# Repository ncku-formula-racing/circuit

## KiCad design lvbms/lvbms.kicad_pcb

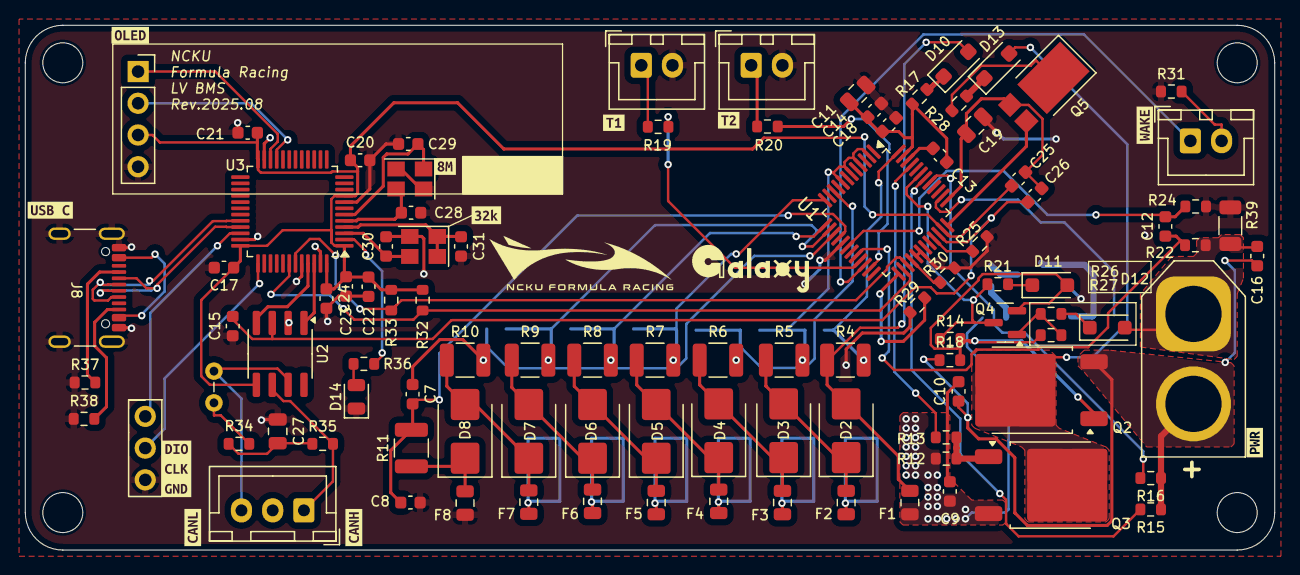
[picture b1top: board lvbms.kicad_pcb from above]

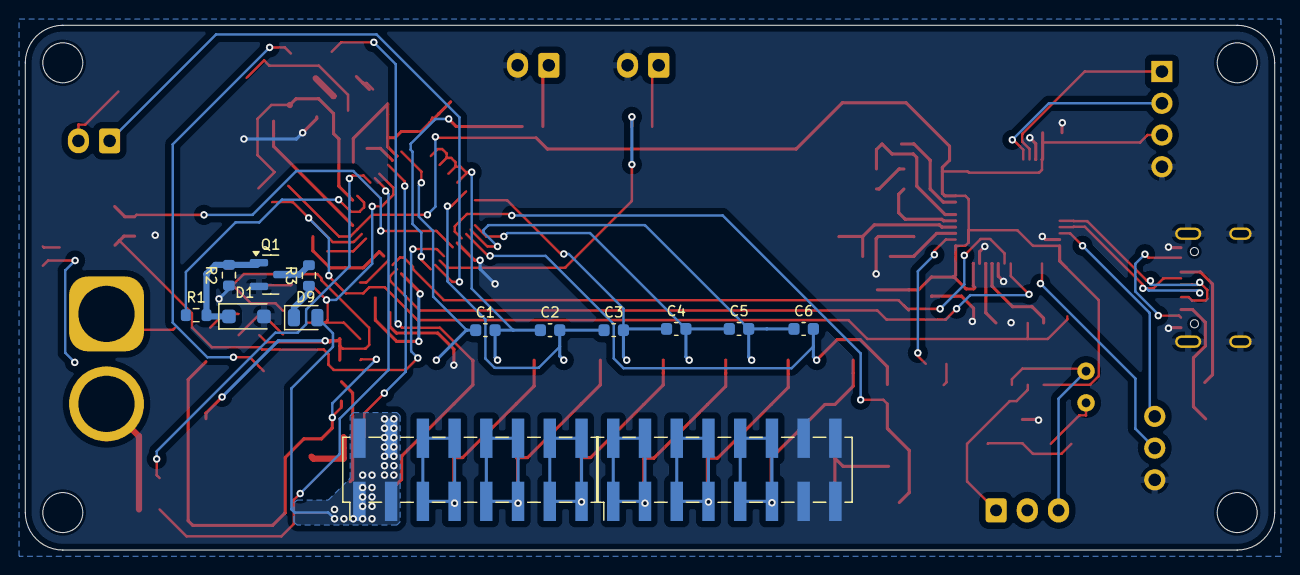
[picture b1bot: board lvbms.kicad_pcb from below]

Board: 2 copper layers, 100.0 x 42.0 mm, 127 parts (14 on the bottom side), 83 nets.

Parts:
C1, C2, C3, C4, C5, C6, C7, C8: 220n; C_0603_1608Metric
C9, C10, C12, C15, C16, C17, C20, C21, C22, C23, C24: 100n; C_0603_1608Metric
C11, C19, C27: 1u; C_0805_2012Metric
C13, C14: 470n; C_0603_1608Metric
C18: 100p; C_0603_1608Metric
C25, C26: 22n; C_0603_1608Metric
C28, C29, C30, C31: 20p; C_0603_1608Metric
D1: BZT52C6V2-13-F; D_SOD-123F
D2, D3, D4, D5, D6, D7, D8: SMBJ55.0CA; D_SMB
D9: PWR_LED; LED_0805_2012Metric
D10, D11, D12, D13: BAT46W-7-F; D_SOD-123F
D14: RUN_GREEN; LED_0805_2012Metric
F1, F2, F3, F4, F5, F6, F7, F8: 0.5A Fuse; Fuse_0805_2012Metric
H1, H2, H3, H4: MountingHole; MountingHole_3.2mm_M3_DIN965
J1: Conn_T1; JST_XH_B2B-XH-A_1x02_P2.50mm_Vertical
J2: Conn_T2; JST_XH_B2B-XH-A_1x02_P2.50mm_Vertical
J3: Conn_PWR; AMASS_XT60-M_1x02_P7.20mm_Vertical
J4: Conn_CAN; JST_XH_B3B-XH-A_1x03_P2.50mm_Vertical
J5: Conn_WAKE; JST_XH_B2B-XH-A_1x02_P2.50mm_Vertical
J6: Conn_OLED; PinSocket_1x04_P2.54mm_Vertical
J7: PROG; PinHeader_1x03_P2.54mm_Vertical
J8: USB_C_Receptacle_USB2.0_16P; USB_C_Receptacle_GCT_USB4105-xx-A_16P_TopMnt_Horizontal
J9, J10: Conn_02x08_Counter_Clockwise; PinHeader_2x08_P2.54mm_Vertical_SMD
JP1: Jumper_2_Open; Jumper_P2.54mm_D0.7mm
Q1, Q4: 2N7002; SOT-23
Q2, Q3: DMN6040SK3; TO-252-2
Q5: DXT5551P5; D_PowerDI-5
R1, R13, R37, R38: 5k1; R_0603_1608Metric
R2: 20k; R_0603_1608Metric
R3, R14, R15, R16, R19, R20, R26, R31, R32, R33: 10k; R_0603_1608Metric
R4, R5, R6, R7, R8, R9, R10, R11: 100R; R_1210_3225Metric
R12, R18, R27: 10M; R_0603_1608Metric
R17, R28: 100R; R_0603_1608Metric
R21: 7k5; R_0603_1608Metric
R22, R24: 100; R_0603_1608Metric
R25, R29, R30, R36: 1k; R_0603_1608Metric
R34, R35: 60R; R_0603_1608Metric
R39: PMR18EZPJV1L0; R_1206_3216Metric
U1: BQ76942PFBR; TQFP-48_7x7mm_P0.5mm
U2: SN65HVD256D; SOIC-8_3.9x4.9mm_P1.27mm
U3: STM32F103C8Tx; LQFP-48_7x7mm_P0.5mm
Y1: 8M; Crystal_SMD_SeikoEpson_FA238-4Pin_3.2x2.5mm
Y2: 32.768k; Crystal_SMD_SeikoEpson_FA238-4Pin_3.2x2.5mm
kibuzzard-6889FCBA: G***; kibuzzard-6889FCBA
kibuzzard-6889FCC4: G***; kibuzzard-6889FCC4
kibuzzard-6889FCCC: G***; kibuzzard-6889FCCC
kibuzzard-6889FCDE: G***; kibuzzard-6889FCDE
kibuzzard-6889FCF3: G***; kibuzzard-6889FCF3
kibuzzard-6889FCFB: G***; kibuzzard-6889FCFB
kibuzzard-6889FD0D: G***; kibuzzard-6889FD0D
kibuzzard-6889FD3D: G***; kibuzzard-6889FD3D
kibuzzard-6889FD5F: G***; kibuzzard-6889FD5F
kibuzzard-6889FD6C: G***; kibuzzard-6889FD6C
kibuzzard-6889FD35: G***; kibuzzard-6889FD35

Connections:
+3V3: C17.2, C20.1, C21.1, C22.1, C23.1, C24.1, C25.1, J6.3, R32.1, R33.1, U1.35 (REG1), U2.5 (VRXD), U3.1 (VBAT), U3.9 (VDDA), U3.24 (VDD), U3.36 (VDD), U3.48 (VDD)
+5V: C15.2, C26.1, U1.34 (REG2), U2.3 (VCC)
-VDC: C16.2, D12.2 (A), J3.1, R22.2, R39.1
/CELL_A1: F7.1, J10.9, J10.10, J10.11, J10.12
/CELL_A2: F6.1, J10.5, J10.6, J10.7, J10.8
/CELL_A3: F5.1, J10.1, J10.2, J10.3, J10.4
/CELL_A4: F4.1, J9.13, J9.14, J9.15, J9.16
/CELL_A5: F3.1, J9.9, J9.10, J9.11, J9.12
/CELL_A6: F2.1, J9.5, J9.6, J9.7, J9.8
/CELL_A7: C9.1, D9.2 (A), F1.1, J9.1, J9.2, J9.3, J9.4, Q2.3 (S), R12.1
/LSE_IN: C30.1, U3.3 (PC14), Y2.3
/LSE_OUT: C31.1, U3.4 (PC15), Y2.1, Y2.4
/VC_A0: C7.2, C8.1, R11.2, U1.16 (VC0)
/VC_A1: C6.2, C7.1, R10.2, U1.15 (VC1)
/VC_A2: C5.2, C6.1, R9.2, U1.14 (VC2)
/VC_A3: C4.2, C5.1, R8.2, U1.13 (VC3)
/VC_A4: C3.2, C4.1, R7.2, U1.12 (VC4)
/VC_A5: C2.2, C3.1, R6.2, U1.10 (VC5)
/VC_A6: C1.2, C2.1, R5.2, U1.2 (VC9), U1.4 (VC8), U1.6 (VC7), U1.8 (VC6)
/VC_A7: C1.1, R4.2, U1.48 (VC10)
CAN_N: J4.1, R35.1, U2.6 (CANL)
CAN_P: J4.3, JP1.1 (A), U2.7 (CANH)
CAN_RX: U2.4 (RXD), U3.45 (PB8)
CAN_TX: U2.1 (TXD), U3.46 (PB9)
CD: D13.2 (A), Q2.2 (D), Q3.2 (D)
CHG: R13.1, U1.45 (CHG)
CP1: C13.1, U1.46 (CP1)
DSG: Q4.3 (D), R14.1, R21.1, U1.43 (DSG)
FUSE: R1.1, U1.38 (FUSE)
GND: C8.2, C11.2, C14.2, C15.1, C17.1, C18.2, C19.2, C20.2, C21.2, C22.2, C23.2, C24.2, C27.1, C28.2, C29.2, C30.2, C31.2, D1.2 (A), D14.1 (K), F8.1, J1.2, J2.2, J6.4, J7.3, J8.A1 (GND), J8.A12 (GND), J8.B1 (GND), J8.B12 (GND), J8.S1 (SHIELD), J10.13, J10.14, J10.15, J10.16, Q1.2 (S), R2.1, R24.2, R25.1, R29.2, R30.2, R31.2, R37.1, R38.1, R39.2, U1.17 (VSS), U1.29 (CFETOFF), U1.30 (DFETOFF), U2.2 (GND), U3.8 (VSSA), U3.23 (VSS), U3.35 (VSS), U3.44 (BOOT0), U3.47 (VSS), Y1.2, Y1.4, Y2.2
LD: R16.2, U1.41 (LD)
unnamed: C9.2, C10.1
unnamed: C27.2, R34.1, R35.2
unnamed: D1.1 (K), Q1.1 (G), R1.2, R2.2
unnamed: D2.1 (A1), D3.2 (A2), F2.2, R5.1
unnamed: D3.1 (A1), D4.2 (A2), F3.2, R6.1
unnamed: D4.1 (A1), D5.2 (A2), F4.2, R7.1
unnamed: D5.1 (A1), D6.2 (A2), F5.2, R8.1
unnamed: D6.1 (A1), D7.2 (A2), F6.2, R9.1
unnamed: D7.1 (A1), D8.2 (A2), F7.2, R10.1
unnamed: D8.1 (A1), F8.2, R11.1
unnamed: D9.1 (K), R3.1
unnamed: D2.2 (A2), D10.2 (A), F1.2, R4.1
unnamed: D10.1 (K), R17.1
unnamed: D11.2 (A), Q3.1 (G), Q4.2 (S), R14.2, R18.2, R27.1
unnamed: D11.1 (K), R21.2
unnamed: D12.1 (K), R26.1
unnamed: D13.1 (K), R28.2
unnamed: D14.2 (A), R36.1
unnamed: J1.1, R19.1
unnamed: J2.1, R20.1
unnamed: C10.2, C16.1, J3.2, Q3.3 (S), R15.1, R16.1, R18.1
unnamed: J5.1, U1.22 (TS2)
unnamed: J5.2, R31.1
unnamed: J8.A5 (CC1), R37.2
unnamed: J8.B5 (CC2), R38.2
unnamed: JP1.2 (B), R34.2
unnamed: Q1.3 (D), R3.2
unnamed: Q2.1 (G), R12.2, R13.2
unnamed: Q4.1 (G), R26.2, R27.2
unnamed: C19.1, C25.2, C26.2, Q5.2 (B), U1.37 (BREG)
unnamed: Q5.1 (C), R28.1
unnamed: Q5.3 (E), U1.36 (REGIN)
unnamed: R29.1, U1.25 (ALERT)
unnamed: C11.1, C13.2, C14.1, C18.1, R17.2, U1.47 (BAT)
unnamed: R30.1, U1.28 (HDQ)
unnamed: R25.2, U1.33 (RST_SHUT)
unnamed: R32.2, U1.26 (SCL), U3.42 (PB6)
unnamed: R33.2, U1.27 (SDA), U3.43 (PB7)
unnamed: C12.1, R22.1, U1.20 (SRN)
unnamed: C12.2, R24.1, U1.18 (SRP)
unnamed: C28.1, U3.5 (PD0), Y1.3
unnamed: C29.1, U3.6 (PD1), Y1.1
PACK: R15.2, U1.42 (PACK)
RUN_LED: R36.2, U3.2 (PC13)
SCL: J6.2, U3.21 (PB10)
SDA: J6.1, U3.22 (PB11)
SWCLK: J7.2, U3.37 (PA14)
SWDIO: J7.1, U3.34 (PA13)
TS1: R19.2, U1.21 (TS1)
TS3: R20.2, U1.23 (TS3)
USB_D+: J8.A6 (D+), J8.B6 (D+), U3.32 (PA11)
USB_D-: J8.A7 (D-), J8.B7 (D-), U3.33 (PA12)

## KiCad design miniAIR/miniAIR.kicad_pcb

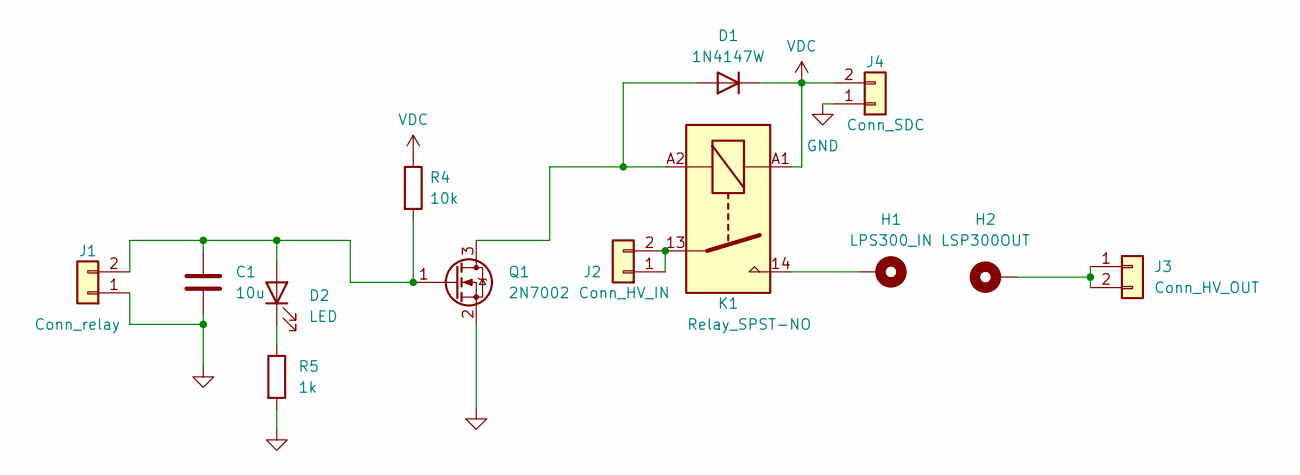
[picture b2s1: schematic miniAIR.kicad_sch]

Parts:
C1: 10u; C_0805_2012Metric
D1: 1N4147W; D_SOD-123F
D2: LED; LED_0805_2012Metric
H1: LPS300_IN; MountingHole_4.3mm_M4_Pad
H2: LSP300OUT; MountingHole_4.3mm_M4_Pad
J1: Conn_relay; JST_XH_B2B-XH-A_1x02_P2.50mm_Vertical
J2: Conn_HV_IN; Molex_Micro-Fit_3.0_43650-0200_1x02_P3.00mm_Horizontal
J3: Conn_HV_OUT; Molex_Micro-Fit_3.0_43650-0200_1x02_P3.00mm_Horizontal
J4: Conn_SDC; JST_XH_B2B-XH-A_1x02_P2.50mm_Vertical
K1: Relay_SPST-NO; KT24-1A-40L-THT
Q1: 2N7002; SOT-23
R4: 10k; R_0603_1608Metric
R5: 1k; R_0603_1608Metric

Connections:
GND: C1.2, J1.1, J4.1, Q1.2 (S), R5.2
unnamed: D1.2 (A), K1.A2, Q1.3 (D)
unnamed: C1.1, D2.2 (A), J1.2, Q1.1 (G), R4.2
unnamed: D2.1 (K), R5.1
unnamed: H1.1, K1.14
unnamed: J2.1, J2.2, K1.13
unnamed: H2.1, J3.1, J3.2
VDC: D1.1 (K), J4.2, K1.A1, R4.1

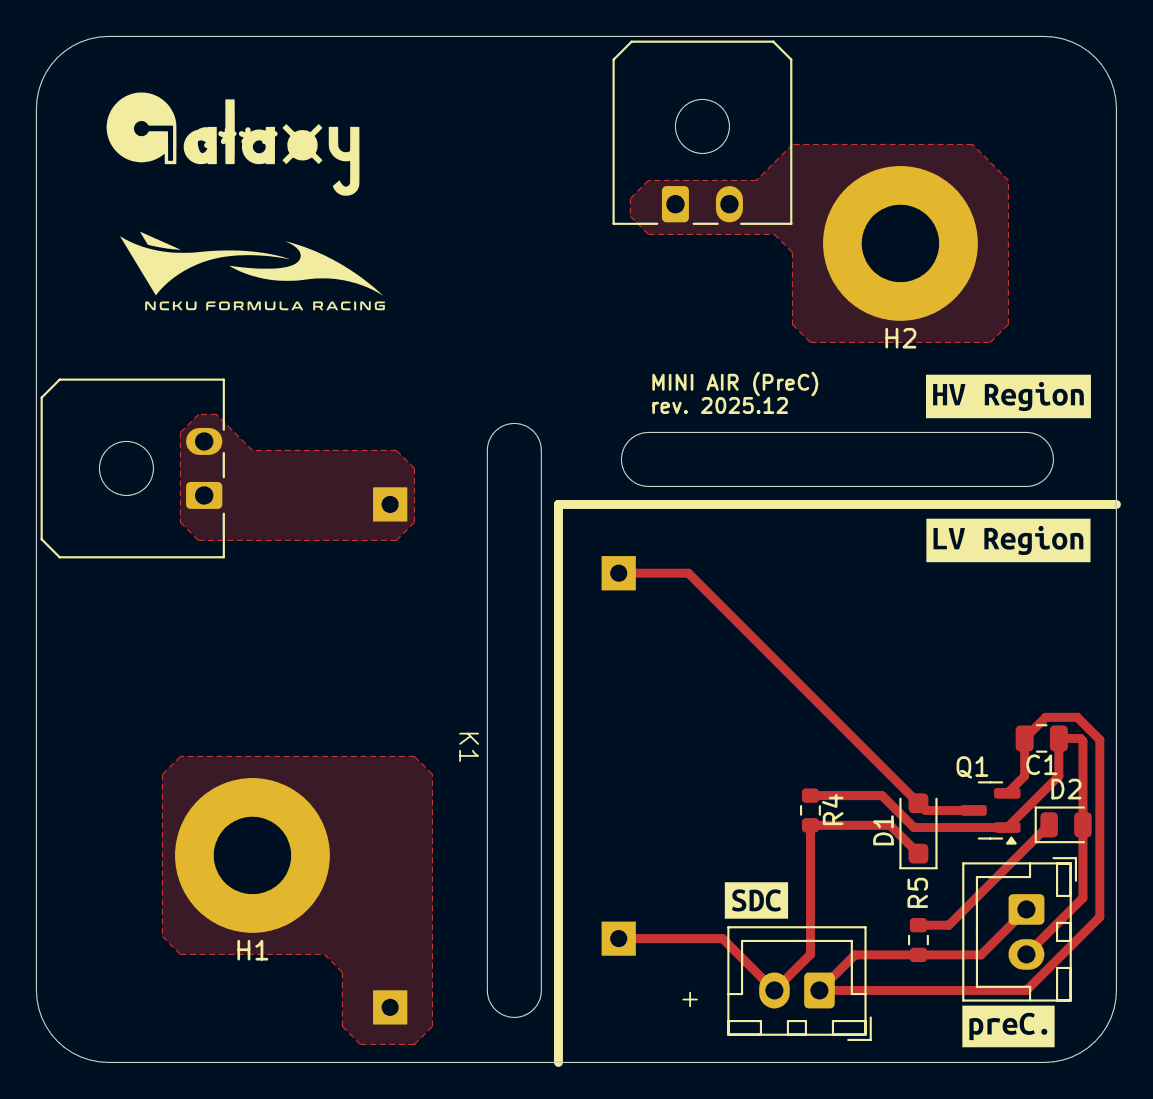
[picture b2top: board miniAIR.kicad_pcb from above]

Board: 2 copper layers, 60.0 x 57.0 mm, 17 parts (0 on the bottom side), 8 nets.

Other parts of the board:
kibuzzard-67D18FBA: G***; kibuzzard-67D18FBA
kibuzzard-680B4203: G***; kibuzzard-680B4203
kibuzzard-69513D2F: G***; kibuzzard-69513D2F
kibuzzard-69513D27: G***; kibuzzard-69513D27

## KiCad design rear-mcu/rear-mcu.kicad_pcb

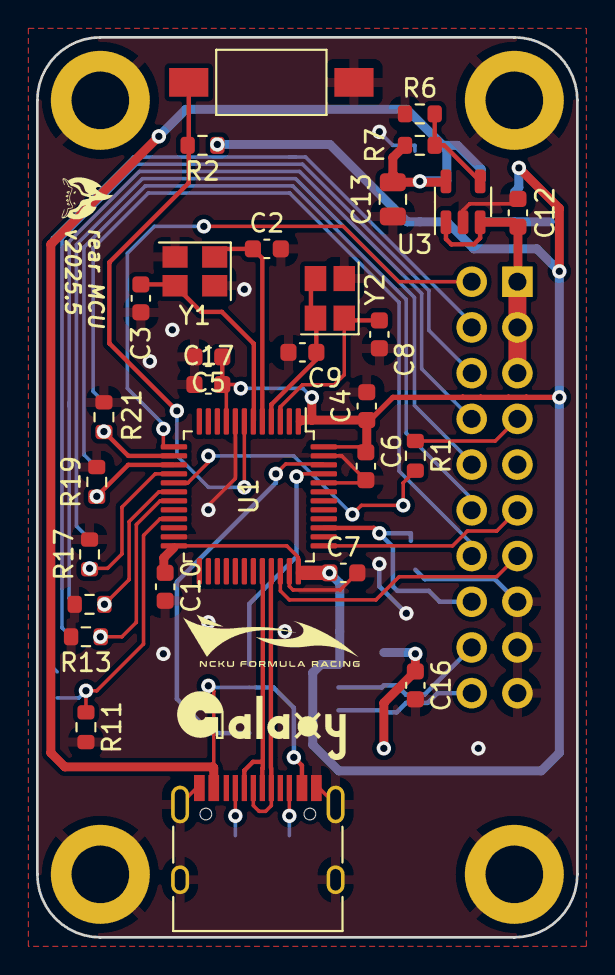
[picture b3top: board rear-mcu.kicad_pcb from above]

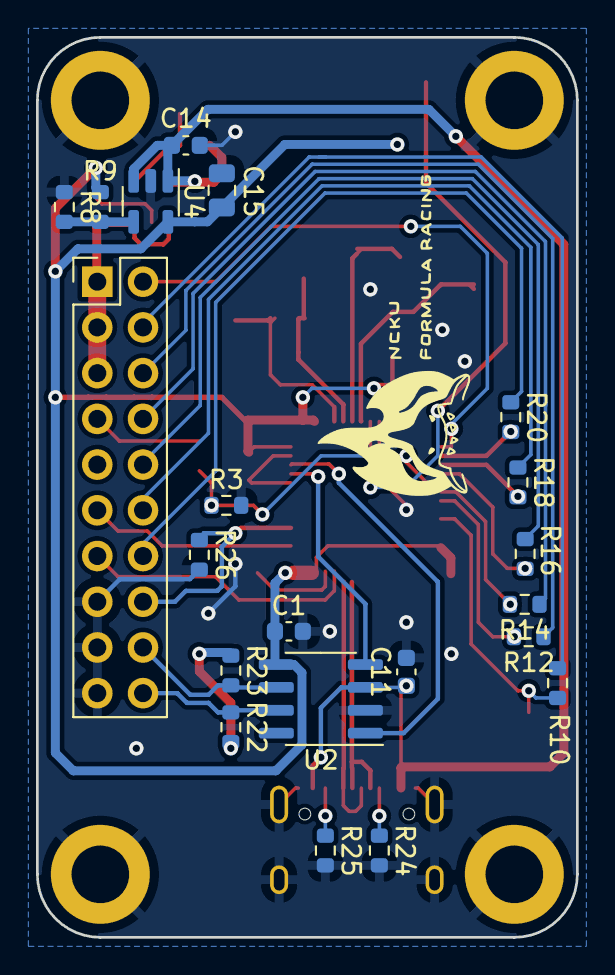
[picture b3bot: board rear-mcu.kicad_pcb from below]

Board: 2 copper layers, 30.0 x 50.0 mm, 54 parts (21 on the bottom side), 38 nets.

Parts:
C1, C4, C6, C7, C10, C11, C17: 100n; C_0603_1608Metric
C2, C3, C8, C9: 20p; C_0603_1608Metric
C5, C12, C14, C16: 1u; C_0603_1608Metric
C13, C15: 10u; C_0805_2012Metric
H1, H2, H3, H4: MountingHole_Pad; MountingHole_3.2mm_M3_ISO14580_Pad
J1: Conn_02x10_Odd_Even; PinHeader_2x10_P2.54mm_Vertical
J2: USB_C_Receptacle_USB2.0_16P; USB_C_Receptacle_HRO_TYPE-C-31-M-12
R1, R10, R12, R14, R16, R18, R20, R26: 47k; R_0603_1608Metric
R2: 10k; R_0603_1608Metric
R3, R6, R8, R11, R13, R15, R17, R19, R21: 100k; R_0603_1608Metric
R7: 866k; R_0603_1608Metric
R9: 165k; R_0603_1608Metric
R22, R23: 60R; R_0603_1608Metric
R24, R25: 5k1; R_0603_1608Metric
SW1: SW_SPST; SW_SPST_FSMSM
U1: STM32F103C8Tx; LQFP-48_7x7mm_P0.5mm
U2: SN65HVD256D; SOIC-8_3.9x4.9mm_P1.27mm
U3, U4: AP2204K-ADJ; SOT-23-5
Y1: 8M; Crystal_SMD_SeikoEpson_FA238-4Pin_3.2x2.5mm
Y2: 32.768k; Crystal_SMD_SeikoEpson_FA238-4Pin_3.2x2.5mm

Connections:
+3.3V: C1.1, C4.1, C5.1, C6.1, C7.1, C10.1, C15.1, C17.1, R2.1, R9.1, U1.1 (VBAT), U1.9 (VDDA), U1.24 (VDD), U1.36 (VDD), U1.48 (VDD), U2.5 (VRXD), U4.5 (VOUT)
+5V: C11.1, C13.1, C14.1, J2.A4 (VBUS), J2.A9 (VBUS), J2.B4 (VBUS), J2.B9 (VBUS), R7.1, U2.3 (VCC), U3.5 (VOUT), U4.1 (VIN), U4.3 (EN)
/HSE_IN: C2.1, U1.5 (PD0), Y1.1
/HSE_OUT: C3.1, U1.6 (PD1), Y1.3
/LSE_IN: C8.1, U1.3 (PC14), Y2.1
/LSE_OUT: C9.1, U1.4 (PC15), Y2.3, Y2.4
/RESET: R2.2, SW1.2 (B), U1.7 (NRST)
BMS_Fault: J1.4, R10.1
BMS_LED: R10.2, R11.1, U1.21 (PB10)
BSPD_Check1: R16.2, R17.1, U1.16 (PA6)
BSPD_Check2: R18.2, R19.1, U1.15 (PA5)
BSPD_Check3: R20.2, R21.1, U1.14 (PA4)
BSPD_Check4: R1.2, R3.1, U1.17 (PA7)
BSPD_Fault: J1.8, R14.1
BSPD_LED: R14.2, R15.1, U1.18 (PB0)
BSPD_signal1: J1.10, R16.1
BSPD_signal2: J1.12, R18.1
BSPD_signal3: J1.14, R20.1
BSPD_signal4: J1.7, R1.1
CAN+: J1.20, R22.1, U2.7 (CANH)
CAN-: J1.18, R23.2, U2.6 (CANL)
CAN_RX: U1.45 (PB8), U2.4 (RXD)
CAN_TX: U1.46 (PB9), U2.1 (TXD)
GND: C1.2, C2.2, C3.2, C4.2, C5.2, C6.2, C7.2, C8.2, C9.2, C10.2, C11.2, C12.2, C13.2, C14.2, C15.2, C16.2, C17.2, H1.1, H2.1, H3.1, H4.1, J1.15, J1.17, J1.19, J2.A1 (GND), J2.B1 (GND), J2.S1 (SHIELD), R3.2, R6.1, R8.1, R11.2, R13.2, R15.2, R17.2, R19.2, R21.2, R24.2, R25.2, R26.2, SW1.1 (A), U1.8 (VSSA), U1.23 (VSS), U1.35 (VSS), U1.44 (BOOT0), U1.47 (VSS), U2.2 (GND), U3.2 (GND), U4.2 (GND), Y1.2, Y1.4, Y2.2
IMD_Fault: J1.6, R12.1
IMD_LED: R12.2, R13.1, U1.19 (PB1)
unnamed: C16.1, R22.2, R23.1
unnamed: J2.A5 (CC1), R24.1
unnamed: J2.B5 (CC2), R25.1
unnamed: R6.2, R7.2, U3.4 (ADJ)
unnamed: R8.2, R9.2, U4.4 (ADJ)
SWDCLK: J1.11, U1.37 (PA14)
SWDIO: J1.13, U1.34 (PA13)
SW_signal: J1.2, U1.13 (PA3)
TSSI: J1.16, R26.1, U1.39 (PB3)
USB_D+: J2.A6 (D+), J2.B6 (D+), U1.33 (PA12)
USB_D-: J2.A7 (D-), J2.B7 (D-), U1.32 (PA11)
VDC: C12.1, J1.1, J1.3, J1.5, U3.1 (VIN), U3.3 (EN)

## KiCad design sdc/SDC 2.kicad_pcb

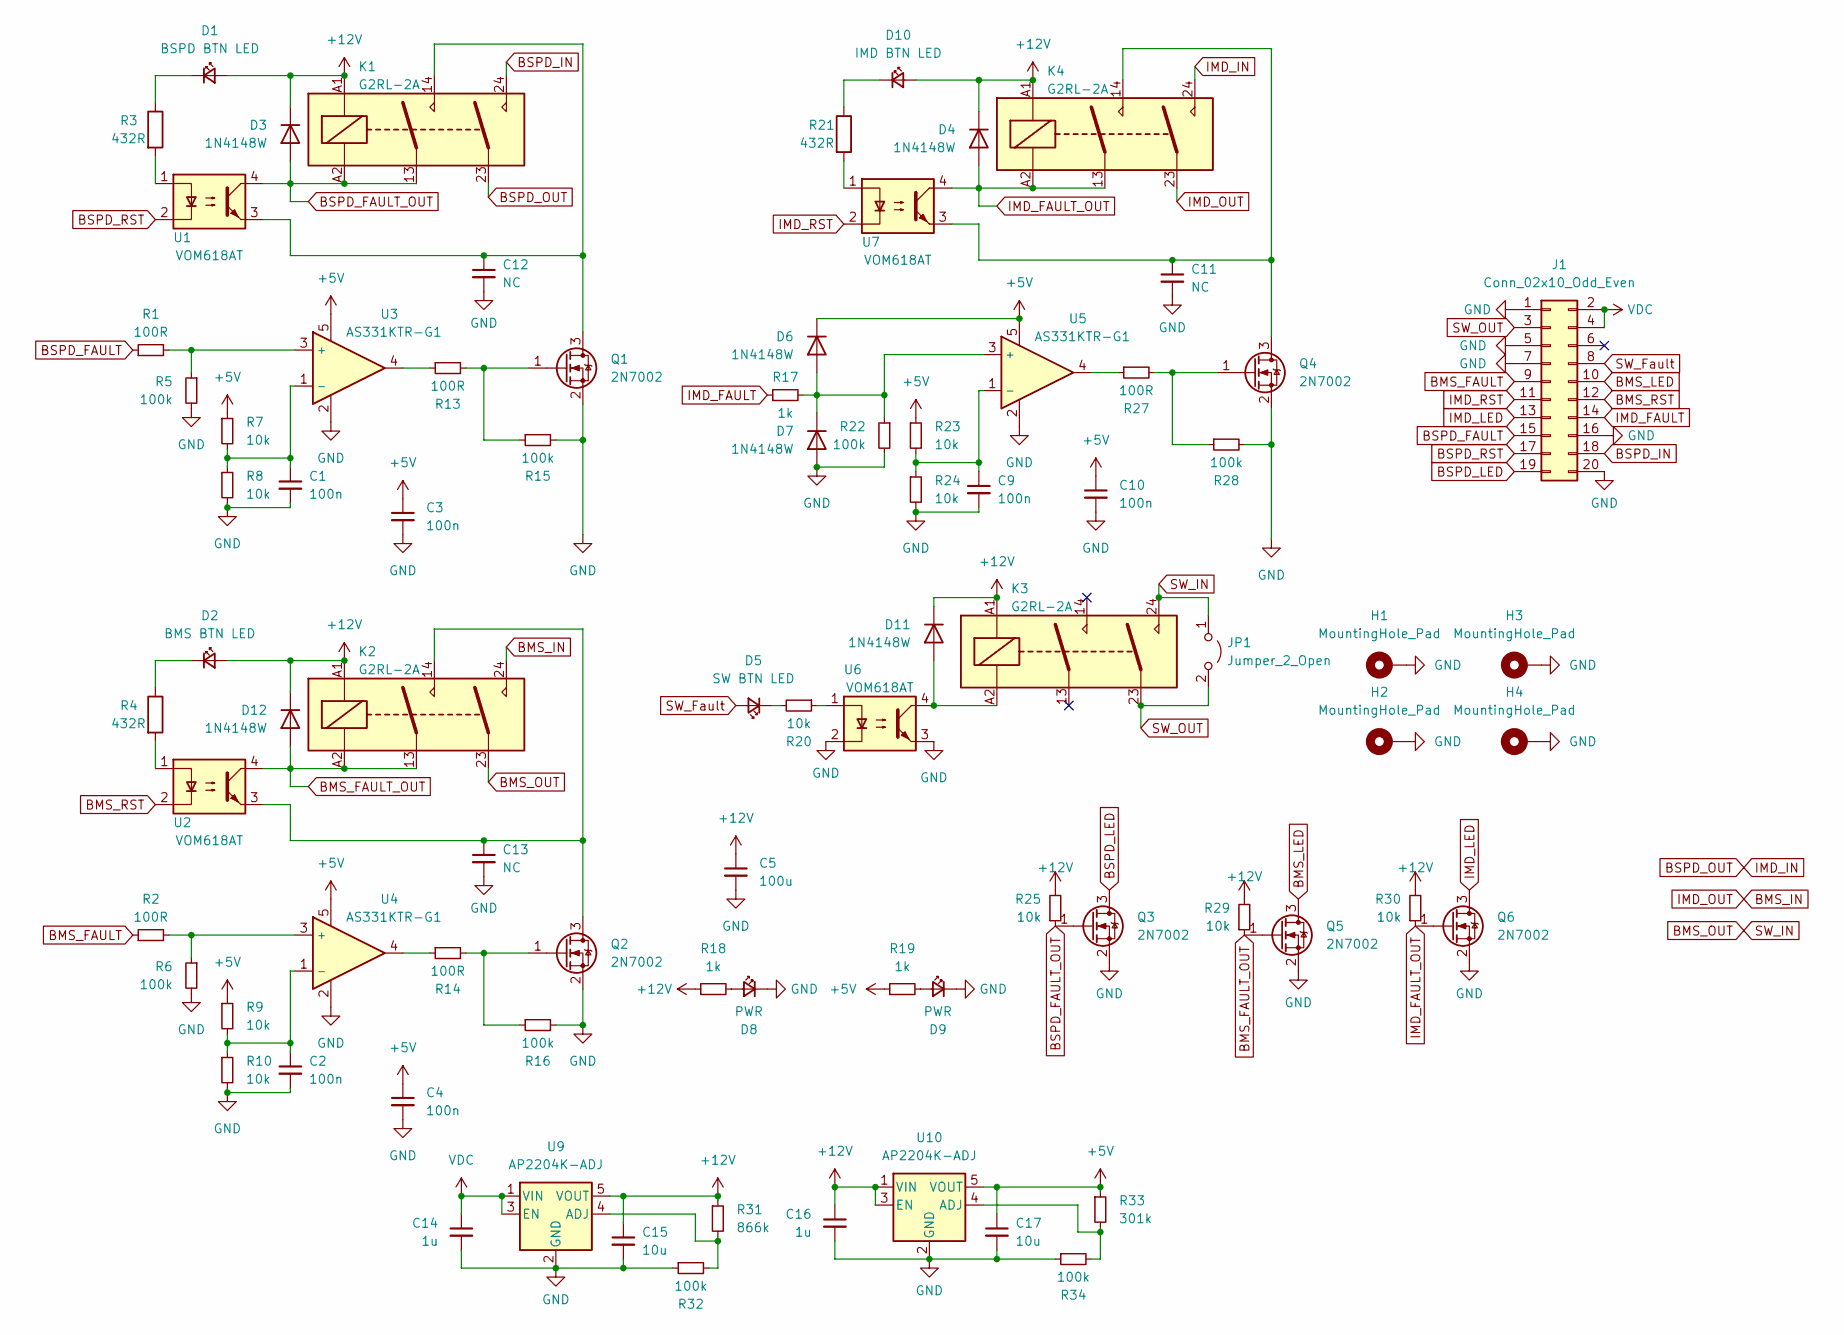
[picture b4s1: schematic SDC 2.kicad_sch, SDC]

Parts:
C1, C2, C3, C4, C9, C10: 100n; C_0603_1608Metric
C5: 100u; C_Radial_D5.0mm_H5.0mm_P2.00mm
C11, C12, C13: NC; C_Disc_D3.0mm_W1.6mm_P2.50mm
C14, C16: 1u; C_0603_1608Metric_Pad1.08x0.95mm_HandSolder
C15, C17: 10u; C_0805_2012Metric_Pad1.18x1.45mm_HandSolder
D1: BSPD BTN LED; LED_0805_2012Metric
D2: BMS BTN LED; LED_0805_2012Metric
D3, D4, D6, D7, D11, D12: 1N4148W; D_SOD-123
D5: SW BTN LED; LED_0805_2012Metric
D8, D9: PWR; LED_0805_2012Metric
D10: IMD BTN LED; LED_0805_2012Metric
H1, H2, H3, H4: MountingHole_Pad; MountingHole_3.2mm_M3_ISO7380_Pad
J1: Conn_02x10_Odd_Even; PinHeader_2x10_P2.54mm_Vertical
JP1: Jumper_2_Open; TestPoint_2Pads_Pitch2.54mm_Drill0.8mm
K1, K2, K3, K4: G2RL-2A; Relay_DPST_Omron_G2RL-2A
Q1, Q2, Q3, Q4, Q5, Q6: 2N7002; SOT-23
R1, R2, R13, R14, R27: 100R; R_0603_1608Metric
R3, R4, R21: 432R; R_0603_1608Metric
R5, R6, R15, R16, R22, R28, R32, R34: 100k; R_0603_1608Metric
R7, R8, R9, R10, R20, R23, R24, R25, R29, R30: 10k; R_0603_1608Metric
R17, R18, R19: 1k; R_0603_1608Metric
R31: 866k; R_0603_1608Metric
R33: 301k; R_0603_1608Metric
U1, U2, U6, U7: VOM618AT; SOP-4_3.8x4.1mm_P2.54mm
U3, U4, U5: AS331KTR-G1; SOT-23-5
U9, U10: AP2204K-ADJ; SOT-23-5

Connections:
+5V: C3.1, C4.1, C10.1, C17.1, D6.1 (K), R7.1, R9.1, R19.1, R23.1, R33.1, U3.5, U4.5, U5.5, U10.5 (VOUT)
+12V: C5.1, C15.1, C16.1, D1.2 (A), D2.2 (A), D3.1 (K), D4.1 (K), D10.2 (A), D11.1 (K), D12.1 (K), K1.A1, K2.A1, K3.A1, K4.A1, R18.1, R25.2, R29.2, R30.2, R31.1, U9.5 (VOUT), U10.1 (VIN), U10.3 (EN)
BMS_FAULT: J1.9, R2.1
BMS_FAULT_OUT: D12.2 (A), K2.13, K2.A2, Q5.1 (G), R29.1, U2.4
BMS_IN: K2.24, K4.23
BMS_LED: J1.10, Q5.3 (D)
BMS_OUT: JP1.1 (A), K2.23, K3.24
BMS_RST: J1.12, U2.2
BSPD_FAULT: J1.15, R1.1
BSPD_FAULT_OUT: D3.2 (A), K1.13, K1.A2, Q3.1 (G), R25.1, U1.4
BSPD_IN: J1.18, K1.24
BSPD_LED: J1.19, Q3.3 (D)
BSPD_OUT: K1.23, K4.24
BSPD_RST: J1.17, U1.2
GND: C1.2, C2.2, C3.2, C4.2, C5.2, C9.2, C10.2, C11.2, C12.2, C13.2, C14.2, C15.2, C16.2, C17.2, D7.2 (A), D8.1 (K), D9.1 (K), H1.1, H2.1, H3.1, H4.1, J1.1, J1.5, J1.7, J1.16, J1.20, Q1.2 (S), Q2.2 (S), Q3.2 (S), Q4.2 (S), Q5.2 (S), Q6.2 (S), R5.2, R6.2, R8.2, R10.2, R15.2, R16.2, R22.2, R24.2, R28.2, R32.1, R34.1, U3.2, U4.2, U5.2, U6.2, U6.3, U9.2 (GND), U10.2 (GND)
IMD_FAULT: J1.14, R17.1
IMD_FAULT_OUT: D4.2 (A), K4.13, K4.A2, Q6.1 (G), R30.1, U7.4
IMD_LED: J1.13, Q6.3 (D)
IMD_RST: J1.11, U7.2
unnamed: D1.1 (K), R3.1
unnamed: D2.1 (K), R4.1
unnamed: D5.1 (K), R20.2
unnamed: D6.2 (A), D7.1 (K), R17.2, R22.1, U5.3 (+)
unnamed: D8.2 (A), R18.2
unnamed: D9.2 (A), R19.2
unnamed: D10.1 (K), R21.1
unnamed: D11.2 (A), K3.A2, U6.4
unnamed: C12.1, K1.14, Q1.3 (D), U1.3
unnamed: Q1.1 (G), R13.2, R15.1
unnamed: C13.1, K2.14, Q2.3 (D), U2.3
unnamed: Q2.1 (G), R14.2, R16.1
unnamed: C11.1, K4.14, Q4.3 (D), U7.3
unnamed: Q4.1 (G), R27.2, R28.1
unnamed: R3.2, U1.1
unnamed: R4.2, U2.1
unnamed: R13.1, U3.4
unnamed: R14.1, U4.4
unnamed: R20.1, U6.1
unnamed: R21.2, U7.1
unnamed: R27.1, U5.4
unnamed: R1.2, R5.1, U3.3 (+)
unnamed: C1.1, R7.2, R8.1, U3.1 (-)
unnamed: R2.2, R6.1, U4.3 (+)
unnamed: C2.1, R9.2, R10.1, U4.1 (-)
unnamed: C9.1, R23.2, R24.1, U5.1 (-)
unnamed: R31.2, R32.2, U9.4 (ADJ)
unnamed: R33.2, R34.2, U10.4 (ADJ)
SW_Fault: D5.2 (A), J1.8
SW_OUT: J1.3, JP1.2 (B), K3.23
VDC: C14.1, J1.2, J1.4, U9.1 (VIN), U9.3 (EN)

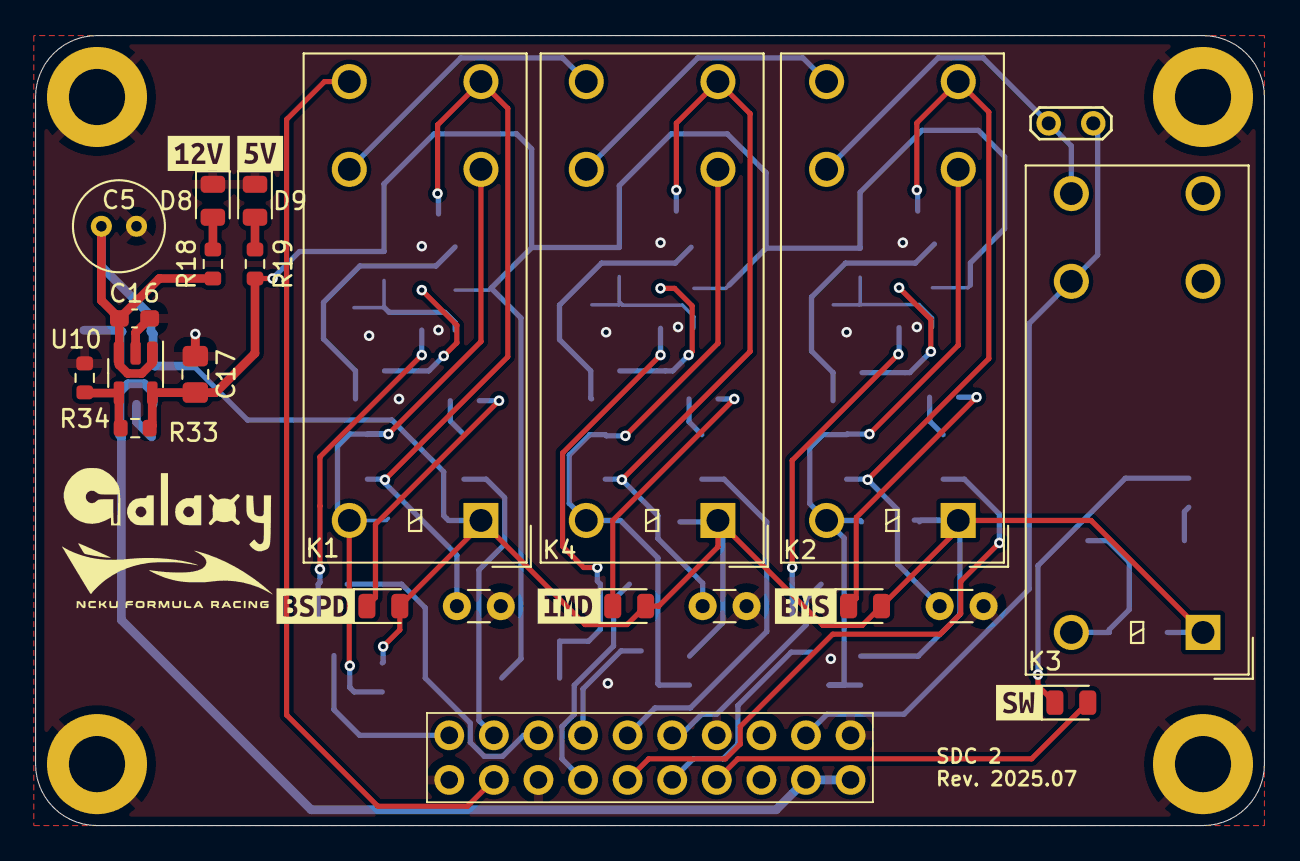
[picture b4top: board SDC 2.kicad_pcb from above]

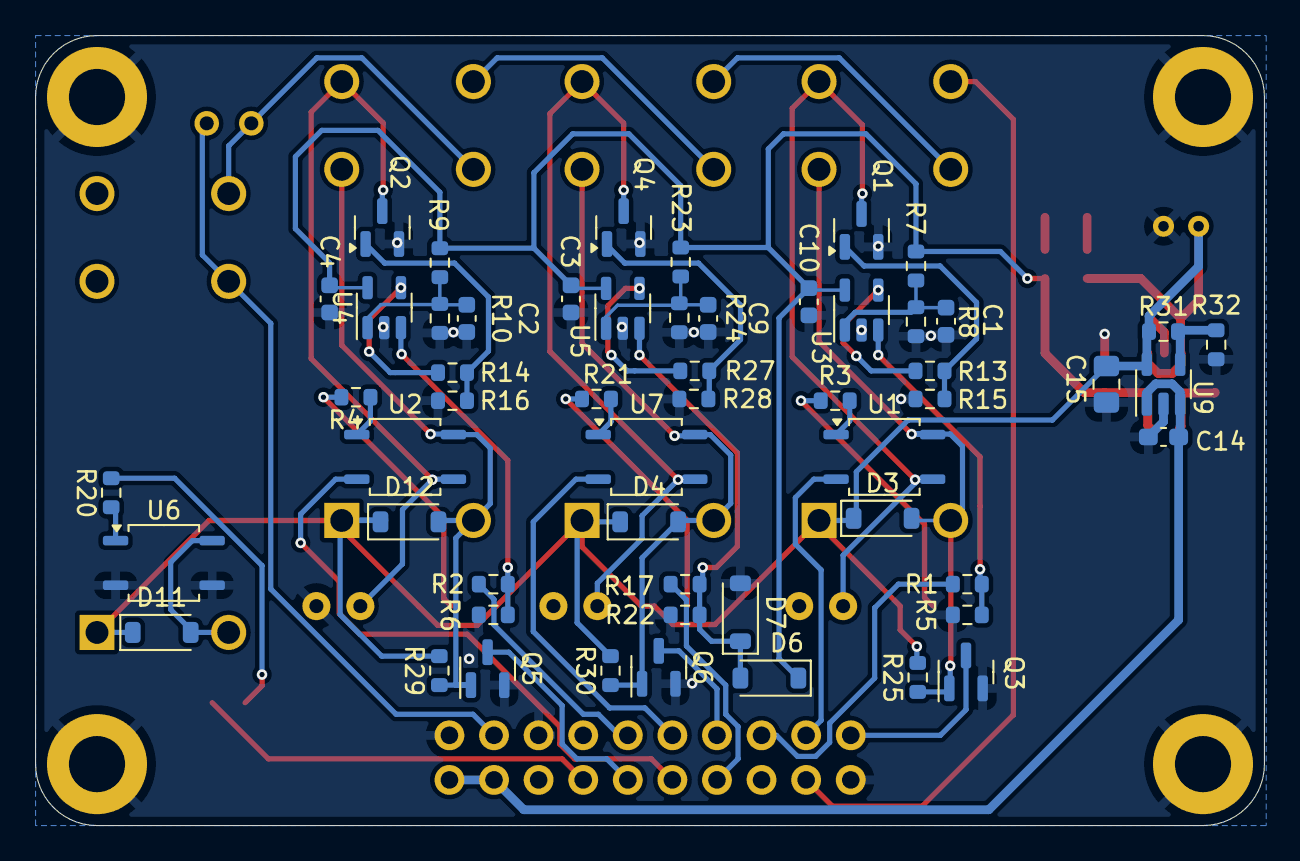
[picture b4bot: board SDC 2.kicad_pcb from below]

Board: 2 copper layers, 70.0 x 45.0 mm, 88 parts (55 on the bottom side), 50 nets.

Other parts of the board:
kibuzzard-67D10362: G***; kibuzzard-67D10362
kibuzzard-67515B78: G***; kibuzzard-67515B78
kibuzzard-67515B81: G***; kibuzzard-67515B81
kibuzzard-67515B89: G***; kibuzzard-67515B89
kibuzzard-67515DEB: G***; kibuzzard-67515DEB
kibuzzard-67515DF6: G***; kibuzzard-67515DF6

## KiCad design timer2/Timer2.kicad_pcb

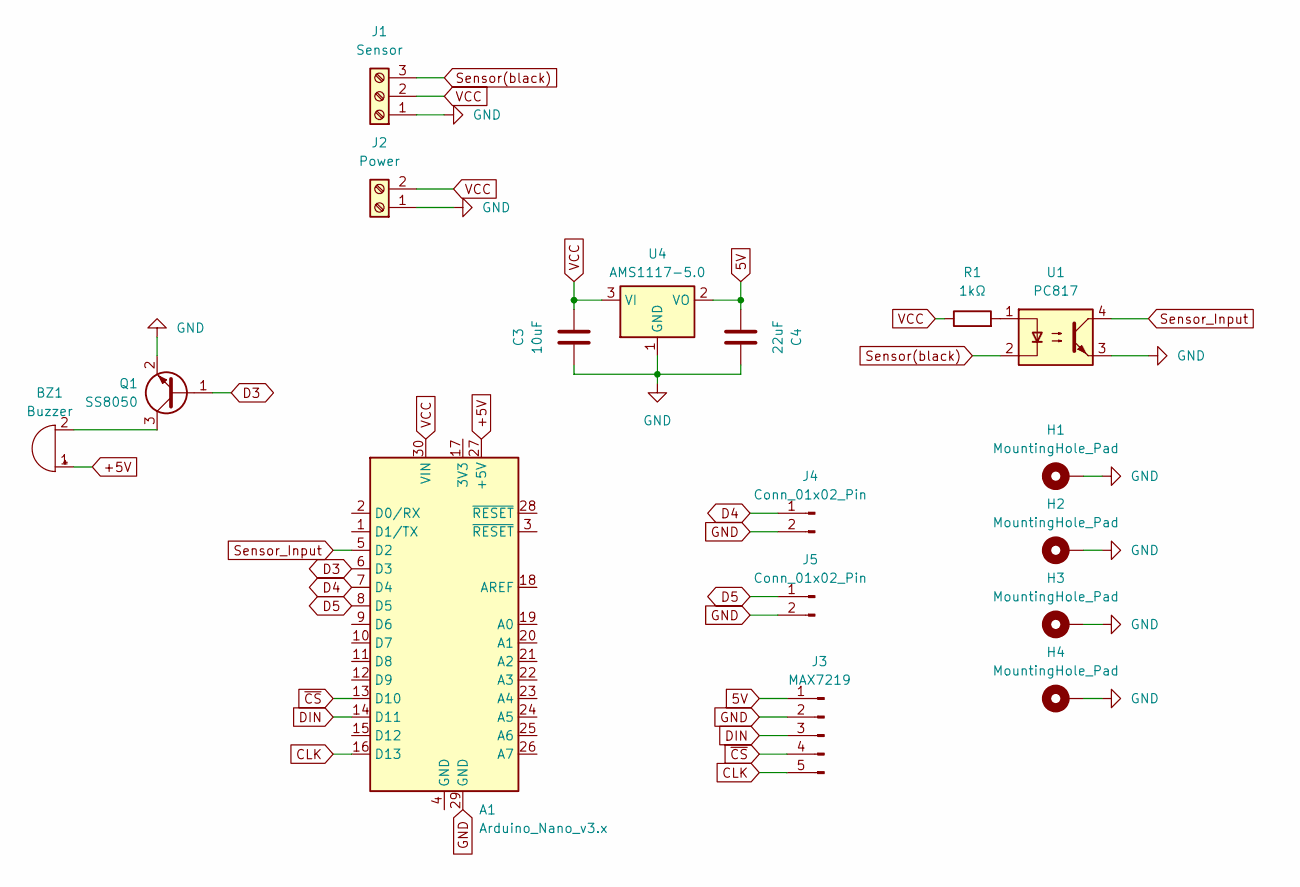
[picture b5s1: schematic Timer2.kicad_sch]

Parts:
A1: Arduino_Nano_v3.x; Arduino_Nano
BZ1: Buzzer; Buzzer_12x9.5RM7.6
C3: 10uF; C_0805_2012Metric
C4: 22uF; C_0805_2012Metric
H1, H2, H3, H4: MountingHole_Pad; MountingHole_3.2mm_M3_ISO14580_Pad
J1: Sensor; TerminalBlock_Phoenix_PT-1,5-3-5.0-H_1x03_P5.00mm_Horizontal
J2: Power; TerminalBlock_Phoenix_PT-1,5-2-5.0-H_1x02_P5.00mm_Horizontal
J3: MAX7219; PinHeader_1x05_P2.54mm_Vertical
J4, J5: Conn_01x02_Pin; PinHeader_1x02_P2.54mm_Vertical
Q1: SS8050; SOT-23
R1: 1kΩ; R_0603_1608Metric
U1: PC817; DIP-4_W7.62mm
U4: AMS1117-5.0; SOT-223-3_TabPin2

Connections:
5V: C4.2, J3.1, U4.2 (VO)
+5V: A1.27 (+5V), BZ1.1 (+)
CLK: A1.16 (D13), J3.5
D3: A1.6 (D3), Q1.1 (B)
D4: A1.7 (D4), J4.1
D5: A1.8 (D5), J5.1
DIN: A1.14 (D11), J3.3
GND: A1.29 (GND), C3.2, C4.1, H1.1, H2.1, H3.1, H4.1, J1.1, J2.1, J3.2, J4.2, J5.2, Q1.2 (E), U1.3, U4.1 (GND)
unnamed: BZ1.2 (-), Q1.3 (C)
unnamed: R1.2, U1.1
Sensor(black): J1.3, U1.2
Sensor_Input: A1.5 (D2), U1.4
VCC: A1.30 (VIN), C3.1, J1.2, J2.2, R1.1, U4.3 (VI)
~CS: A1.13 (D10), J3.4

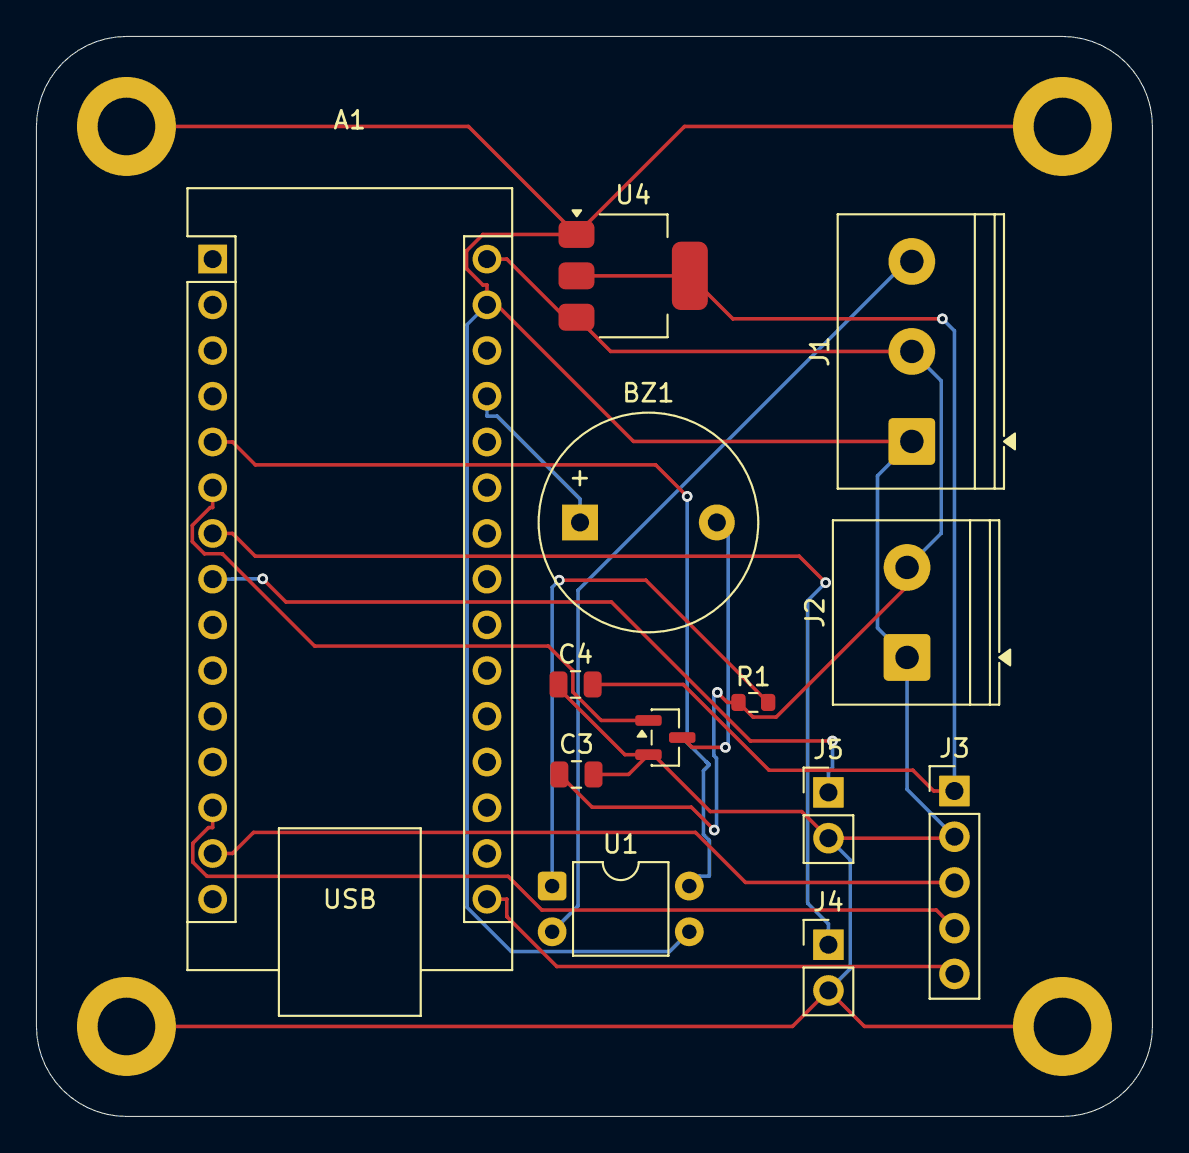
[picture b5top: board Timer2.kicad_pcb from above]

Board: 2 copper layers, 62.0 x 60.0 mm, 17 parts (0 on the bottom side), 14 nets.
